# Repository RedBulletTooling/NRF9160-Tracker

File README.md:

# NRF9160-Tracker
This is hardware project concept of a CR2032 Operated small size LTE-M/NB-Iot GPS tracker 19x26mm
## Reason
We created these designs and products for our company www.menura.org. If you are in need of custom hardware, software and or solutions that provide digital insights  - please contact us at contact@menura.org 

For us, it's one of those products that would be pretty cool to make but hard to go-to-market with given this only has a very niche legitimate use-case. You will need to provide a back end and front end with adequate independent hosting (could be https://www.traccar.org/). Most tracking providers operate with central servers that they themselves own. They, as sellers, are fully capable of tracking your assets. It doesn't sound all that fun if you realize anyone working at those companies in the right position is fully capable of tracking you and your assets as well if not better than you can. 

Besides that, most trackers are trash or DIY. They use technology from < 2010 and have no single thought for (operational) security or reliability. Using the NRF9160, you now have a small GPS tracker communicating over LTE-M/NB-Iot that uses little energy and can provide the security guarantees you need. Using open-source software (or your in-house C2) you are now also not relient on obscure third party providers.

## Notes
This is a design in concept. This is not yet in production, we are 80% sure this should work as is but still have some things to keep in mind;

1. The antenna design is based on the recommendations of Ignion for EU-based operation. But it is a bit more cramped than they would like. We are unsure of RF performance and this should be tested. We are pretty sure it should work fine we have seen far worse designs in production that work just fine.
2. It's a passive GPS antenna but again design is followed. Unsure of performance.
3. It's a CR2032 battery-based product. Don't expect this to last multiple years. But with proper programming and battery optimization, which the NRF9160 allows for, it should be able to do just fine. We expect 30 days, at the least.
4. Small compromises have been made, and programming is done with a tag connected 6 pin. Debug can be done over those ports either by UART or J-link based debug named RTT. Power is always provided by a battery or external power source threw battery pads.
5. The pads of the battery have shrunken, because of 2 layer design. This shouldn't be a problem, but maybe it could cause some interference on trace running just below it. Those traces aren't that sensitive.
6. Last thing that is pretty major; we are using a 5V LDO that should be able to step up the voltage from the 3V that is received by the battery. Per spec, it should be able to do that just fine but sometimes they don't match the spec.

## Images

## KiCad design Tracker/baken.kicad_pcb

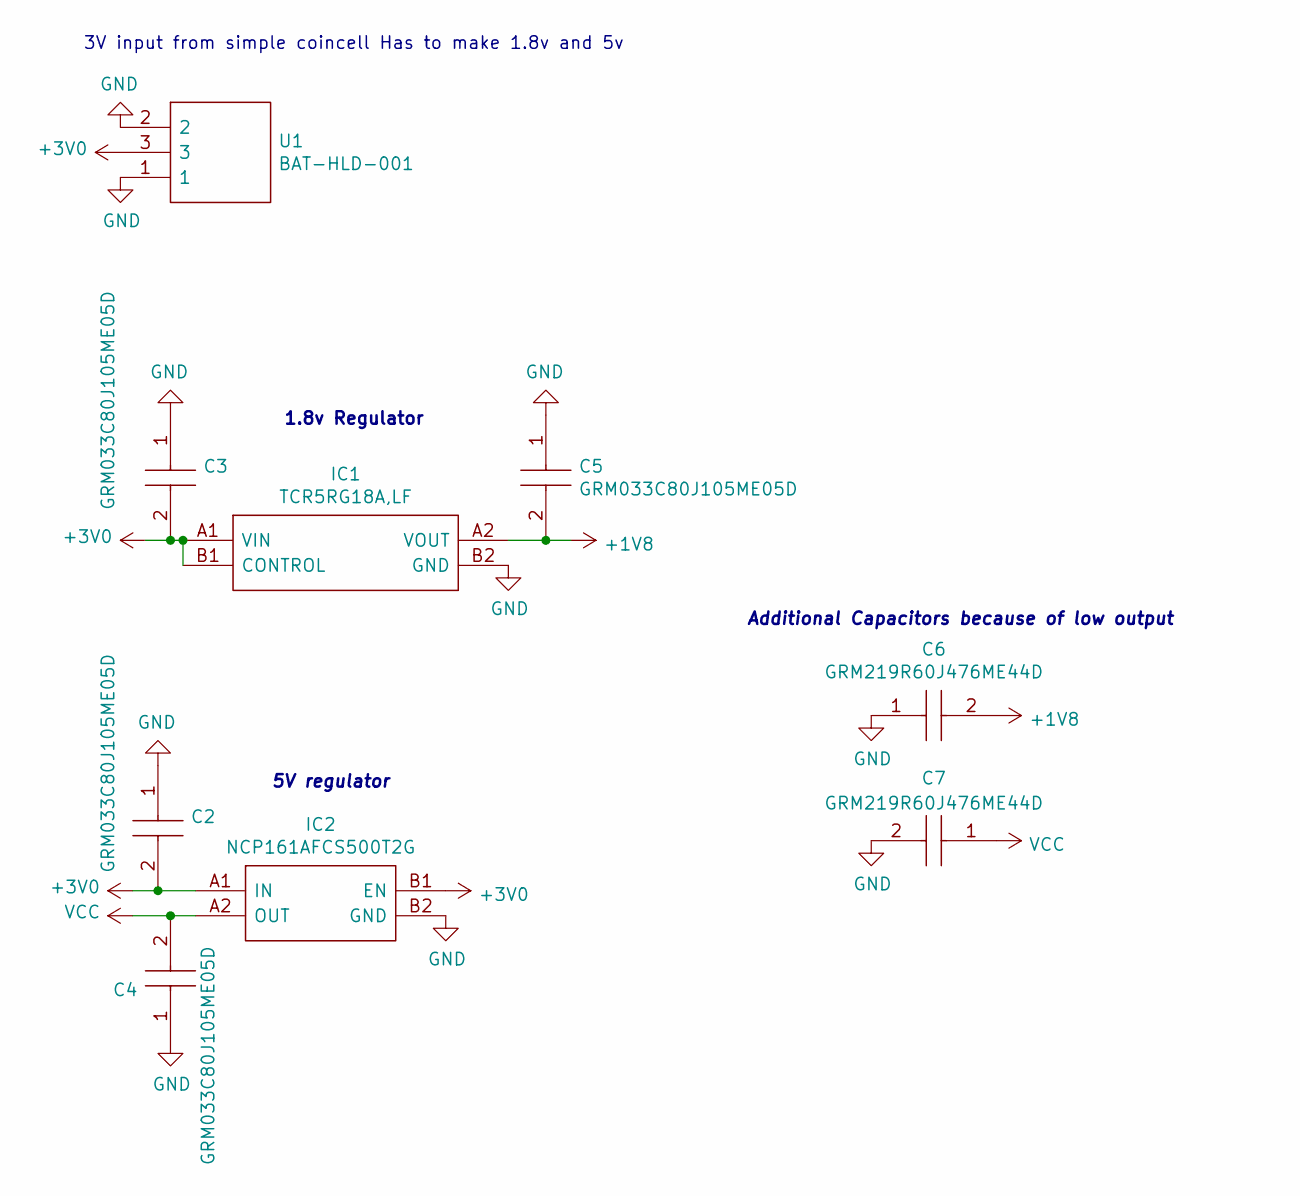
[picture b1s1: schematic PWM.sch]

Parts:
C2, C3, C4, C5: GRM033C80J105ME05D; CAPC0603X33N; Mouser Part Number 81-GRM033C80J105ME5D
C6, C7: GRM219R60J476ME44D; CAPC2012X95N; Mouser Part Number 81-GRM219R60J476ME4D
IC1: TCR5RG18A,LF; TCR5RG18ALF; Manufacturer_Part_Number TCR5RG18A,LF
IC2: NCP161AFCS500T2G; BGA4C35P2X2_64X64X46; Mouser Part Number 863-NCP161AFCS500T2G
U1: BAT-HLD-001; BATHLD001; Mouser Part Number 712-BAT-HLD-001

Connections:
+1V8: C5.2, C6.2, IC1.A2 (VOUT); also elsewhere on the board
+3V0: C2.2, C3.2, IC1.A1 (VIN), IC1.B1 (CONTROL), IC2.A1 (IN), IC2.B1 (EN), U1.3
GND: C2.1, C3.1, C4.1, C5.1, C6.1, C7.2, IC1.B2 (GND), IC2.B2 (GND), U1.1, U1.2; also elsewhere on the board
VCC: C4.2, C7.1, IC2.A2 (OUT); also elsewhere on the board

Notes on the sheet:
3V input from simple coincell Has to make 1.8v and 5v
1.8v Regulator
5V regulator
Additional Capacitors because of low output

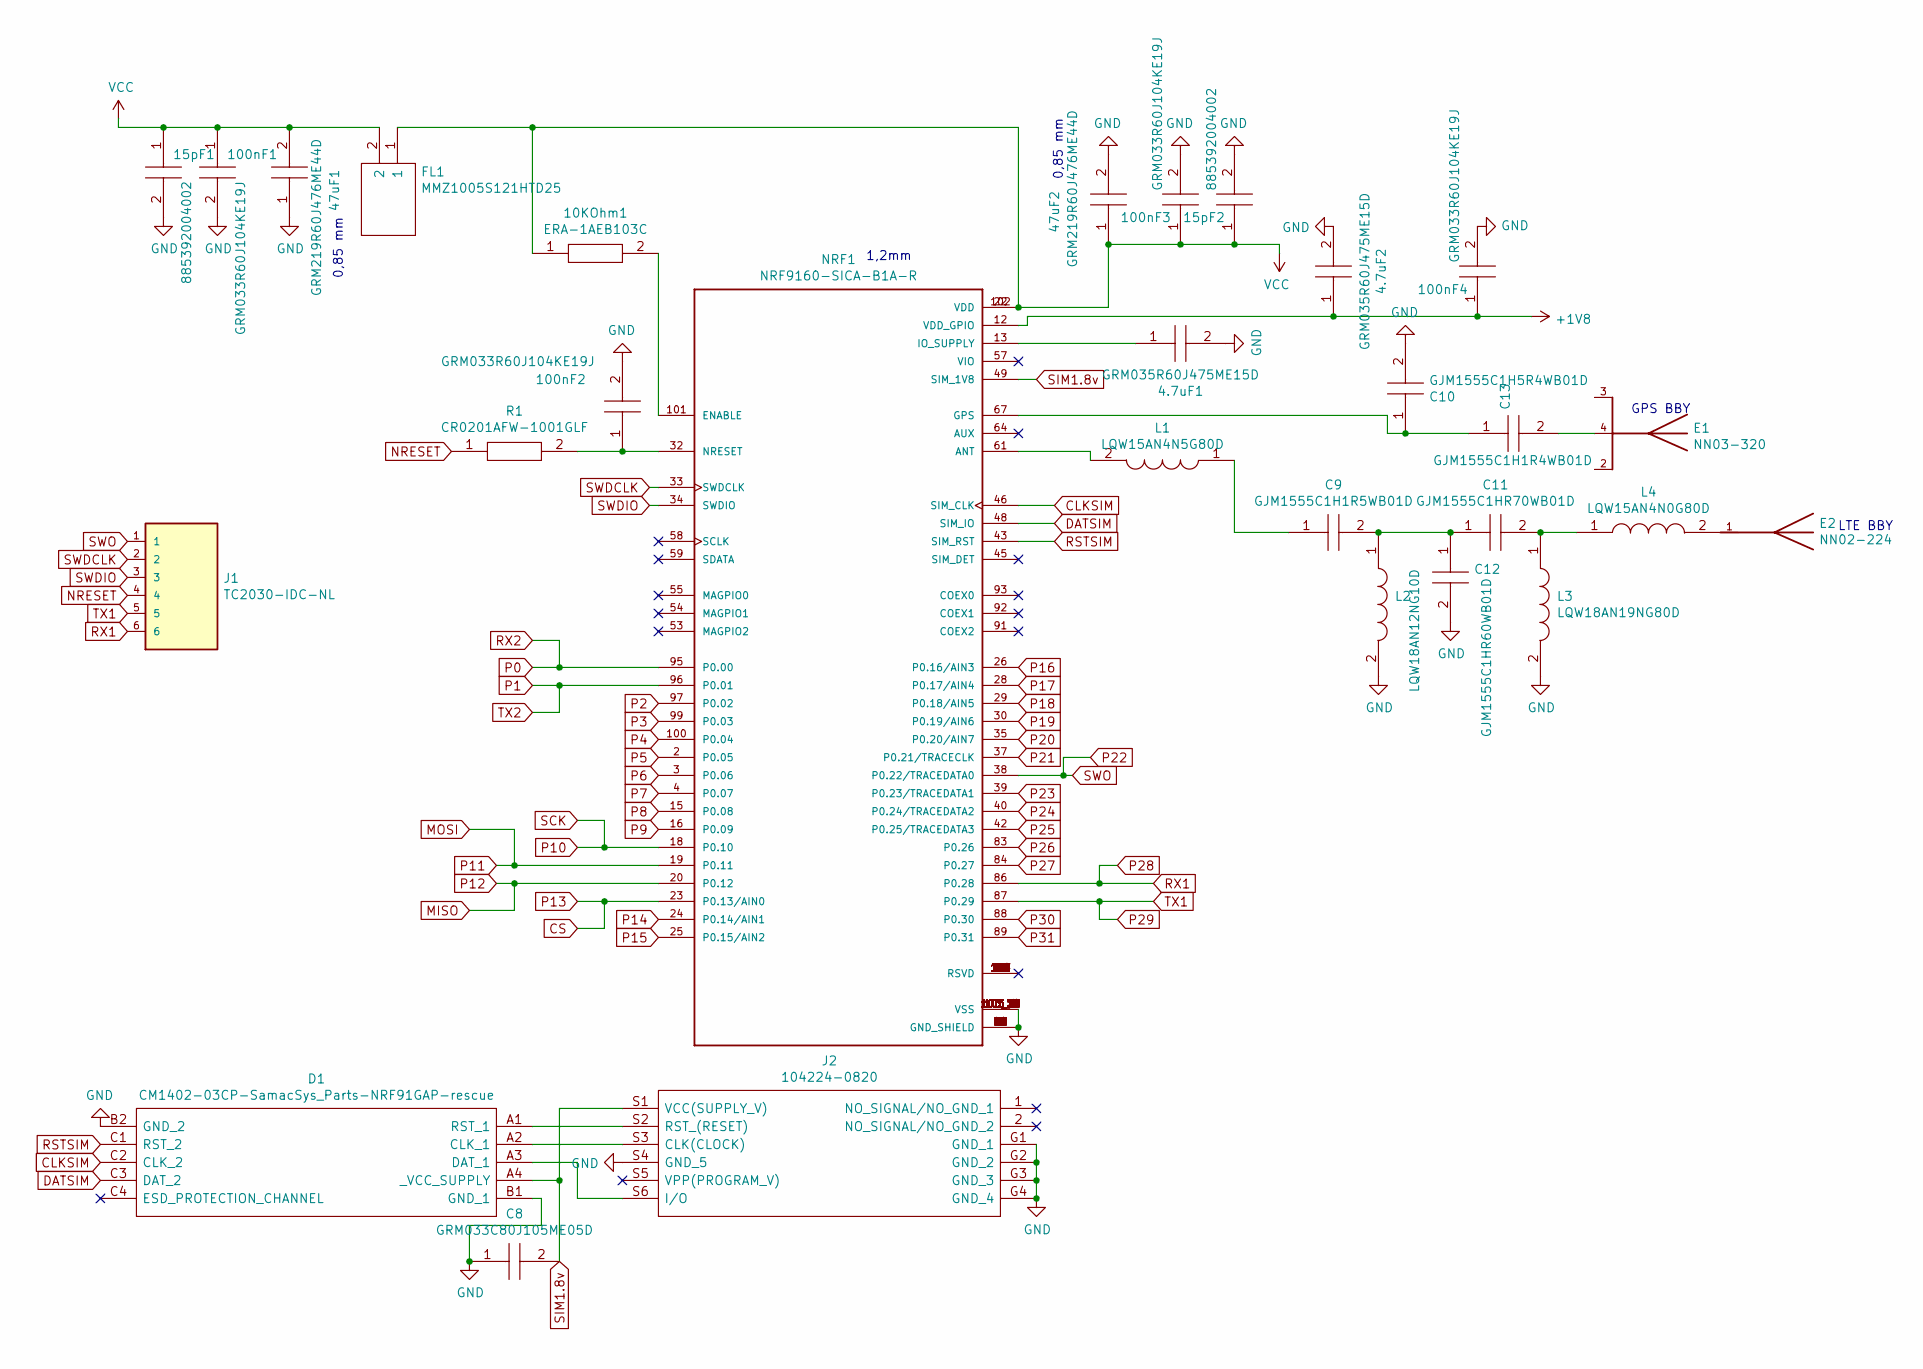
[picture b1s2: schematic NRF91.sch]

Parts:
4.7uF1, 4.7uF2: GRM035R60J475ME15D; CAPC0603X55N; Mouser Part Number 81-GRM035R60J475ME5D
10KOhm1: ERA-1AEB103C; RESC0603X26N; Mouser Part Number 667-ERA-1AEB103C
15pF1, 15pF2: 885392004002; CAPC0603X33N; Mouser Part Number 710-885392004002
47uF1, 47uF2: GRM219R60J476ME44D; CAPC2012X95N; Mouser Part Number 81-GRM219R60J476ME4D
100nF1, 100nF2, 100nF3, 100nF4: GRM033R60J104KE19J; CAPC0603X33N; Mouser Part Number 81-GRM033R60J104KE9J
C8: GRM033C80J105ME05D; CAPC0603X33N; Mouser Part Number 81-GRM033C80J105ME5D
C9: GJM1555C1H1R5WB01D; CAPC1005X55N; Mouser Part Number 81-GJM1555C1H1R5WB1D
C10: GJM1555C1H5R4WB01D; CAPC1005X55N; Mouser Part Number 81-GJM1555C1H5R4WB1D
C11: GJM1555C1HR70WB01D; CAPC1005X55N; Mouser Part Number 81-GJM1555C1HR70WB1D
C12: GJM1555C1HR60WB01D; CAPC1005X55N; Mouser Part Number 81-GJM1555C1HR60WB1D
C13: GJM1555C1H1R4WB01D; CAPC1005X55N; Manufacturer_Part_Number GJM1555C1H1R4WB01D
D1: CM1402-03CP-SamacSys_Parts-NRF91GAP-rescue; CM140203CP; Mouser Part Number 748-CM1402-03CP
E1: NN03-320; XCVR_NN03-320; PARTREV July 2019
E2: NN02-224; XCVR_NN02-224; PARTREV December 2020
FL1: MMZ1005S121HTD25; BEADC1005X55N; Mouser Part Number 810-MMZ1005S121HTD25
J1: TC2030-IDC-NL; TAG_TC2030-IDC-NL; PARTREV MS
J2: 104224-0820; 1042240820; Mouser Part Number 538-104224-0820
L1: LQW15AN4N5G80D; LQW15AN10NG80D; Manufacturer_Part_Number LQW15AN4N5G80D
L2: LQW18AN12NG10D; LQW18AS10NG0CD; Mouser Part Number 81-LQW18AN12NG10D
L3: LQW18AN19NG80D; LQW18AN10NG80D; Mouser Part Number 81-LQW18AN19NG80D
L4: LQW15AN4N0G80D; LQW15AN10NG80D; Manufacturer_Part_Number LQW15AN4N0G80D
NRF1: NRF9160-SICA-B1A-R; XCVR_NRF9160-SICA-R
R1: CR0201AFW-1001GLF; RESC0603X26N; Mouser Part Number 652-CR0201AFW1001GLF

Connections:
+1V8: 4.7uF2.1, 100nF4.1, NRF1.12 (VDD_GPIO); also elsewhere on the board
CLKSIM: D1.C2 (CLK_2), NRF1.46 (SIM_CLK)
CS: NRF1.23 (P0.13/AIN0)
DATSIM: D1.C3 (DAT_2), NRF1.48 (SIM_IO)
GND: 4.7uF1.2, 4.7uF2.2, 15pF1.2, 15pF2.2, 47uF1.1, 47uF2.2, 100nF1.2, 100nF2.2, 100nF3.2, 100nF4.2, C8.1, C10.2, C12.2, D1.B1 (GND_1), D1.B2 (GND_2), J2.G1 (GND_1), J2.G2 (GND_2), J2.G3 (GND_3), J2.G4 (GND_4), J2.S4 (GND_5), L2.2, L3.2, NRF1.1 (GND_SHIELD), NRF1.5 (GND_SHIELD), NRF1.9 (GND_SHIELD), NRF1.14 (GND_SHIELD), NRF1.17 (GND_SHIELD), NRF1.21 (GND_SHIELD), NRF1.27 (GND_SHIELD), NRF1.31 (GND_SHIELD), NRF1.36 (GND_SHIELD), NRF1.41 (GND_SHIELD), NRF1.44 (GND_SHIELD), NRF1.47 (GND_SHIELD), NRF1.50 (GND_SHIELD), NRF1.52 (GND_SHIELD), NRF1.56 (GND_SHIELD), NRF1.60 (GND_SHIELD), NRF1.62 (GND_SHIELD), NRF1.63 (GND_SHIELD), NRF1.65 (GND_SHIELD), NRF1.66 (GND_SHIELD), NRF1.72 (GND_SHIELD), NRF1.74 (GND_SHIELD), NRF1.75 (GND_SHIELD), NRF1.76 (GND_SHIELD), NRF1.77 (GND_SHIELD), NRF1.78 (GND_SHIELD), NRF1.79 (GND_SHIELD), NRF1.80 (GND_SHIELD), NRF1.81 (GND_SHIELD), NRF1.82 (GND_SHIELD), NRF1.85 (GND_SHIELD), NRF1.90 (GND_SHIELD), NRF1.94 (GND_SHIELD), NRF1.98 (GND_SHIELD), NRF1.103_1 (VSS), NRF1.103_2 (VSS), NRF1.103_3 (VSS), NRF1.103_4 (VSS), NRF1.103_5 (VSS), NRF1.103_6 (VSS), NRF1.103_7 (VSS), NRF1.103_8 (VSS), NRF1.103_9 (VSS), NRF1.103_10 (VSS), NRF1.103_11 (VSS), NRF1.103_12 (VSS), NRF1.103_13 (VSS), NRF1.103_14 (VSS), NRF1.103_15 (VSS), NRF1.103_16 (VSS), NRF1.103_17 (VSS), NRF1.103_18 (VSS), NRF1.103_19 (VSS), NRF1.103_20 (VSS), NRF1.103_21 (VSS), NRF1.103_22 (VSS), NRF1.103_23 (VSS), NRF1.103_24 (VSS), NRF1.103_25 (VSS), NRF1.103_26 (VSS), NRF1.103_27 (VSS), NRF1.103_28 (VSS), NRF1.103_29 (VSS), NRF1.103_30 (VSS), NRF1.103_31 (VSS), NRF1.103_32 (VSS), NRF1.103_33 (VSS), NRF1.103_34 (VSS), NRF1.103_35 (VSS); also elsewhere on the board
MISO: NRF1.20 (P0.12)
MOSI: NRF1.19 (P0.11)
NRESET: J1.4, R1.1
unnamed: 4.7uF1.1, NRF1.13 (IO_SUPPLY)
unnamed: 10KOhm1.2, NRF1.101 (ENABLE)
unnamed: 100nF2.1, NRF1.32 (NRESET), R1.2
unnamed: C9.1, L1.1
unnamed: C10.1, C13.1, NRF1.67 (GPS)
unnamed: C9.2, C11.1, C12.1, L2.1
unnamed: C11.2, L3.1, L4.1
unnamed: C13.2, E1.4
unnamed: D1.A1 (RST_1), J2.S2 (RST_(RESET))
unnamed: D1.A2 (CLK_1), J2.S3 (CLK(CLOCK))
unnamed: D1.A3 (DAT_1), J2.S6 (I/O)
unnamed: E2.1, L4.2
unnamed: L1.2, NRF1.61 (ANT)
unnamed: NRF1.6 (RSVD), NRF1.7 (RSVD), NRF1.8 (RSVD), NRF1.10 (RSVD), NRF1.11 (RSVD), NRF1.51 (RSVD), NRF1.68 (RSVD), NRF1.69 (RSVD), NRF1.70 (RSVD), NRF1.71 (RSVD), NRF1.73 (RSVD), NRF1.104 (RSVD), NRF1.105 (RSVD), NRF1.106 (RSVD), NRF1.107 (RSVD), NRF1.108 (RSVD), NRF1.109 (RSVD), NRF1.110 (RSVD), NRF1.111 (RSVD), NRF1.112 (RSVD), NRF1.113 (RSVD), NRF1.114 (RSVD), NRF1.115 (RSVD), NRF1.116 (RSVD), NRF1.117 (RSVD), NRF1.118 (RSVD), NRF1.119 (RSVD), NRF1.120 (RSVD), NRF1.121 (RSVD), NRF1.122 (RSVD), NRF1.123 (RSVD), NRF1.124 (RSVD), NRF1.125 (RSVD), NRF1.126 (RSVD), NRF1.127 (RSVD)
P0: NRF1.95 (P0.00)
P1: NRF1.96 (P0.01)
P2: NRF1.97 (P0.02)
P3: NRF1.99 (P0.03)
P4: NRF1.100 (P0.04)
P5: NRF1.2 (P0.05)
P6: NRF1.3 (P0.06)
P7: NRF1.4 (P0.07)
P8: NRF1.15 (P0.08)
P9: NRF1.16 (P0.09)
P10: NRF1.18 (P0.10)
P14: NRF1.24 (P0.14/AIN1)
P15: NRF1.25 (P0.15/AIN2)
P16: NRF1.26 (P0.16/AIN3)
P17: NRF1.28 (P0.17/AIN4)
P18: NRF1.29 (P0.18/AIN5)
P19: NRF1.30 (P0.19/AIN6)
P20: NRF1.35 (P0.20/AIN7)
P21: NRF1.37 (P0.21/TRACECLK)
P22: J1.1, NRF1.38 (P0.22/TRACEDATA0)
P23: NRF1.39 (P0.23/TRACEDATA1)
P24: NRF1.40 (P0.24/TRACEDATA2)
P25: NRF1.42 (P0.25/TRACEDATA3)
P26: NRF1.83 (P0.26)
P27: NRF1.84 (P0.27)
P28: J1.6, NRF1.86 (P0.28)
P29: J1.5, NRF1.87 (P0.29)
P30: NRF1.88 (P0.30)
P31: NRF1.89 (P0.31)
RSTSIM: D1.C1 (RST_2), NRF1.43 (SIM_RST)
SIM1.8v: C8.2, D1.A4 (_VCC_SUPPLY), J2.S1 (VCC(SUPPLY_V)), NRF1.49 (SIM_1V8)
SWDCLK: J1.2, NRF1.33 (SWDCLK)
SWDIO: J1.3, NRF1.34 (SWDIO)
VCC: 10KOhm1.1, 15pF1.1, 15pF2.1, 47uF1.2, 47uF2.1, 100nF1.1, 100nF3.1, FL1.1, FL1.2, NRF1.22 (VDD), NRF1.102 (VDD); also elsewhere on the board

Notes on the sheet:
0,85 mm
1,2mm
GPS BBY
LTE BBY

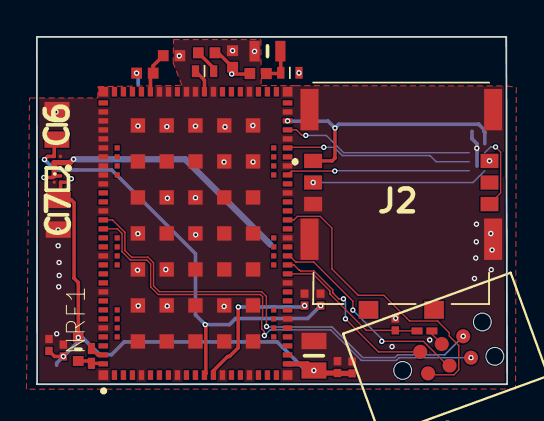
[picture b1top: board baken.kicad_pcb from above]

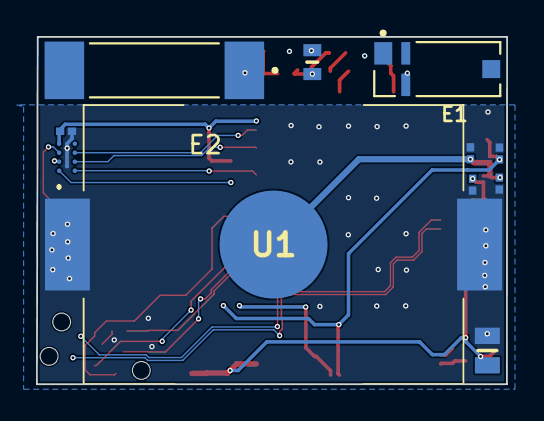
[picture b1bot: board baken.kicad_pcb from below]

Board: 2 copper layers, 26.1 x 19.3 mm, 37 parts (11 on the bottom side), 28 nets.

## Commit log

2024-02-19 Added missing libraries
